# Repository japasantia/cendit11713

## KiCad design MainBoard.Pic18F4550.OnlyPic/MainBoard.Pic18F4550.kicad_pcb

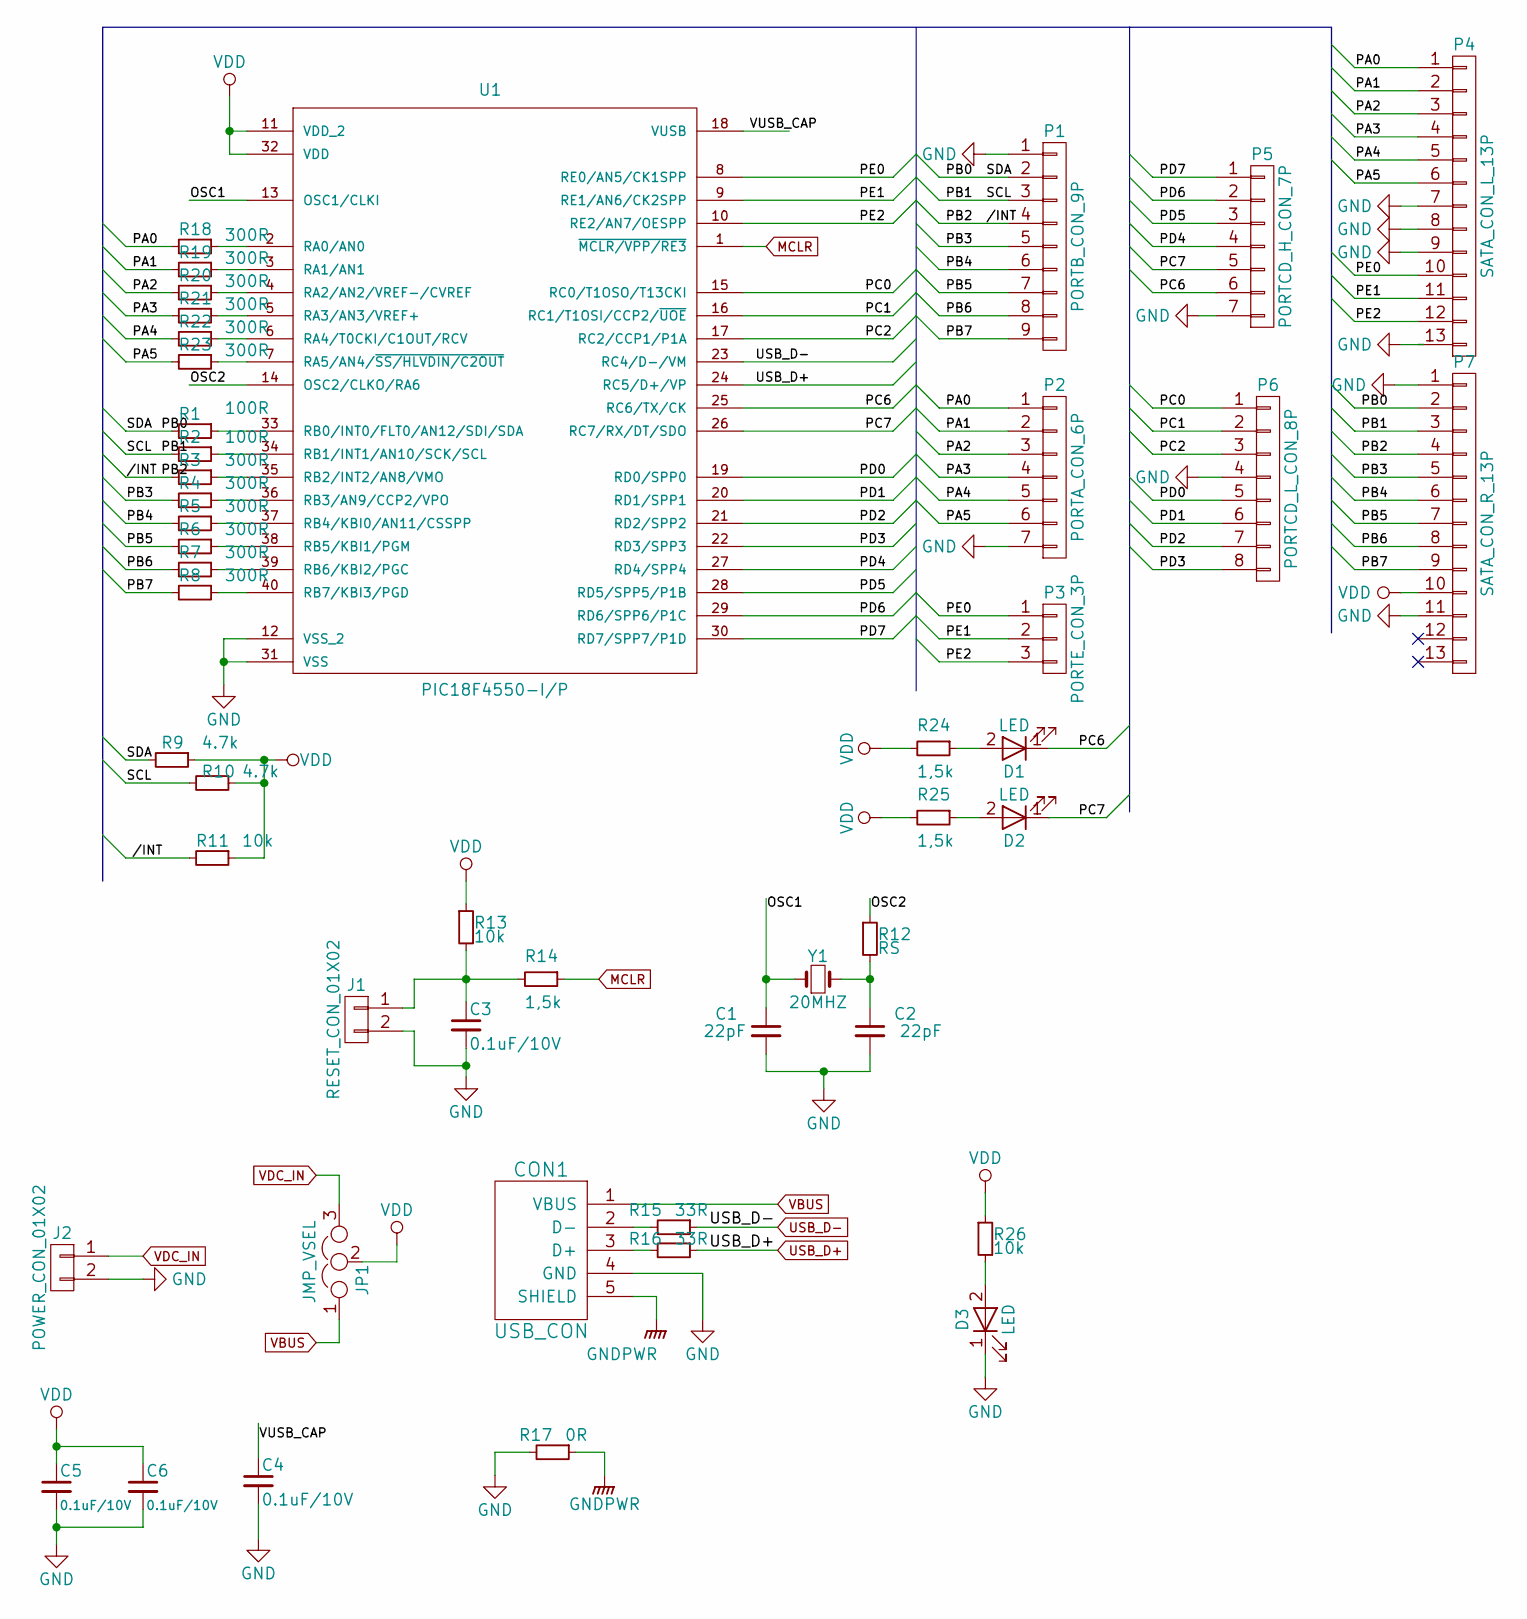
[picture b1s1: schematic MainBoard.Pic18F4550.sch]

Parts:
C1, C2: 22pF; C_0805_HandSoldering
C3, C4: 0.1uF/10V; C_0805_HandSoldering
C5, C6: 0.1uF/10V; C_1206_HandSoldering
CON1: USB_CON; USB_SMT_B
D1, D2, D3: LED; LED_0805
J1: RESET_CON_01X02; Pin_Header_Straight_1x02_Pitch2.54mm
J2: POWER_CON_01X02; Pin_Header_Straight_1x02_Pitch2.54mm
JP1: JMP_VSEL; Pin_Header_Straight_1x03
P1: PORTB_CON_9P; Pin_Header_Straight_1x09
P2: PORTA_CON_6P; Pin_Header_Straight_1x07
P3: PORTE_CON_3P; Pin_Header_Straight_1x03
P4: SATA_CON_L_13P; SLIMLINE_SATA_PLUG_7P_6P
P5: PORTCD_H_CON_7P; Pin_Header_Straight_1x07
P6: PORTCD_L_CON_8P; Pin_Header_Straight_1x08
P7: SATA_CON_R_13P; SATA_RECEPTACLE_VERTICAL_SMT_6P_7P
R1, R2: 100R; R_0805_HandSoldering
R3, R4, R5, R6, R7, R8, R18, R19, R20, R21, R22, R23: 300R; R_0805_HandSoldering
R9, R10: 4.7k; R_0805_HandSoldering
R11, R13, R26: 10k; R_0805_HandSoldering
R12: RS; R_0805_HandSoldering
R14, R24, R25: 1,5k; R_0805_HandSoldering
R15, R16: 33R; R_0805_HandSoldering
R17: 0R; R_0805_HandSoldering
U1: PIC18F4550-I/P; PIC18F4550-PDIP
Y1: 20MHZ; Crystal_SMD_HC49-SD

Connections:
//INT: P1.4, P7.4, R3.2, R11.2
/OSC1: C1.1, U1.13 (OSC1/CLKI), Y1.1
/OSC2: R12.1, U1.14 (OSC2/CLKO/RA6)
/PA0: P2.1, P4.1, R18.2
/PA1: P2.2, P4.2, R19.2
/PA2: P2.3, P4.3, R20.2
/PA3: P2.4, P4.4, R21.2
/PA4: P2.5, P4.5, R22.2
/PA5: P2.6, P4.6, R23.2
/PB0: P1.2, P7.2, R1.2, R9.2
/PB1: P1.3, P7.3, R2.2, R10.2
/PB3: P1.5, P7.5, R4.2
/PB4: P1.6, P7.6, R5.2
/PB5: P1.7, P7.7, R6.2
/PB6: P1.8, P7.8, R7.2
/PB7: P1.9, P7.9, R8.2
/PC0: P6.1, U1.15 (RC0/T1OSO/T13CKI)
/PC1: P6.2, U1.16 (RC1/T1OSI/CCP2/~UOE)
/PC2: P6.3, U1.17 (RC2/CCP1/P1A)
/PC6: D1.1 (K), P5.6, U1.25 (RC6/TX/CK)
/PC7: D2.1 (K), P5.5, U1.26 (RC7/RX/DT/SDO)
/PD0: P6.5, U1.19 (RD0/SPP0)
/PD1: P6.6, U1.20 (RD1/SPP1)
/PD2: P6.7, U1.21 (RD2/SPP2)
/PD3: P6.8, U1.22 (RD3/SPP3)
/PD4: P5.4, U1.27 (RD4/SPP4)
/PD5: P5.3, U1.28 (RD5/SPP5/P1B)
/PD6: P5.2, U1.29 (RD6/SPP6/P1C)
/PD7: P5.1, U1.30 (RD7/SPP7/P1D)
/PE0: P3.1, P4.10, U1.8 (RE0/AN5/CK1SPP)
/PE1: P3.2, P4.11, U1.9 (RE1/AN6/CK2SPP)
/PE2: P3.3, P4.12, U1.10 (RE2/AN7/OESPP)
/VUSB_CAP: C4.1, U1.18 (VUSB)
GND: C1.2, C2.2, C3.2, C4.2, C5.2, C6.2, CON1.4 (GND), D3.1 (K), J1.2, J2.2, P1.1, P2.7, P4.7, P4.8, P4.9, P5.7, P6.4, P7.1, P7.11, R17.2, U1.12 (VSS_2), U1.31 (VSS)
GNDPWR: CON1.5 (SHIELD), R17.1
MCLR: R14.1, U1.1 (~MCLR/VPP/RE3)
unnamed: C2.1, R12.2, Y1.2
unnamed: C3.1, J1.1, R13.2, R14.2
unnamed: CON1.2 (D-), R15.2
unnamed: CON1.3 (D+), R16.2
unnamed: D1.2 (A), R24.1
unnamed: D2.2 (A), R25.1
unnamed: D3.2 (A), R26.2
unnamed: R1.1, U1.33 (RB0/INT0/FLT0/AN12/SDI/SDA)
unnamed: R2.1, U1.34 (RB1/INT1/AN10/SCK/SCL)
unnamed: R3.1, U1.35 (RB2/INT2/AN8/VMO)
unnamed: R4.1, U1.36 (RB3/AN9/CCP2/VPO)
unnamed: R5.1, U1.37 (RB4/KBI0/AN11/CSSPP)
unnamed: R6.1, U1.38 (RB5/KBI1/PGM)
unnamed: R7.1, U1.39 (RB6/KBI2/PGC)
unnamed: R8.1, U1.40 (RB7/KBI3/PGD)
unnamed: R18.1, U1.2 (RA0/AN0)
unnamed: R19.1, U1.3 (RA1/AN1)
unnamed: R20.1, U1.4 (RA2/AN2/VREF-/CVREF)
unnamed: R21.1, U1.5 (RA3/AN3/VREF+)
unnamed: R22.1, U1.6 (RA4/T0CKI/C1OUT/RCV)
unnamed: R23.1, U1.7 (RA5/AN4/~SS/HLVDIN/C2OUT)
USB_D+: R16.1, U1.24 (RC5/D+/VP)
USB_D-: R15.1, U1.23 (RC4/D-/VM)
VBUS: CON1.1 (VBUS), JP1.1
VDC_IN: J2.1, JP1.3
VDD: C5.1, C6.1, JP1.2, P7.10, R9.1, R10.1, R11.1, R13.1, R24.2, R25.2, R26.1, U1.11 (VDD_2), U1.32 (VDD)

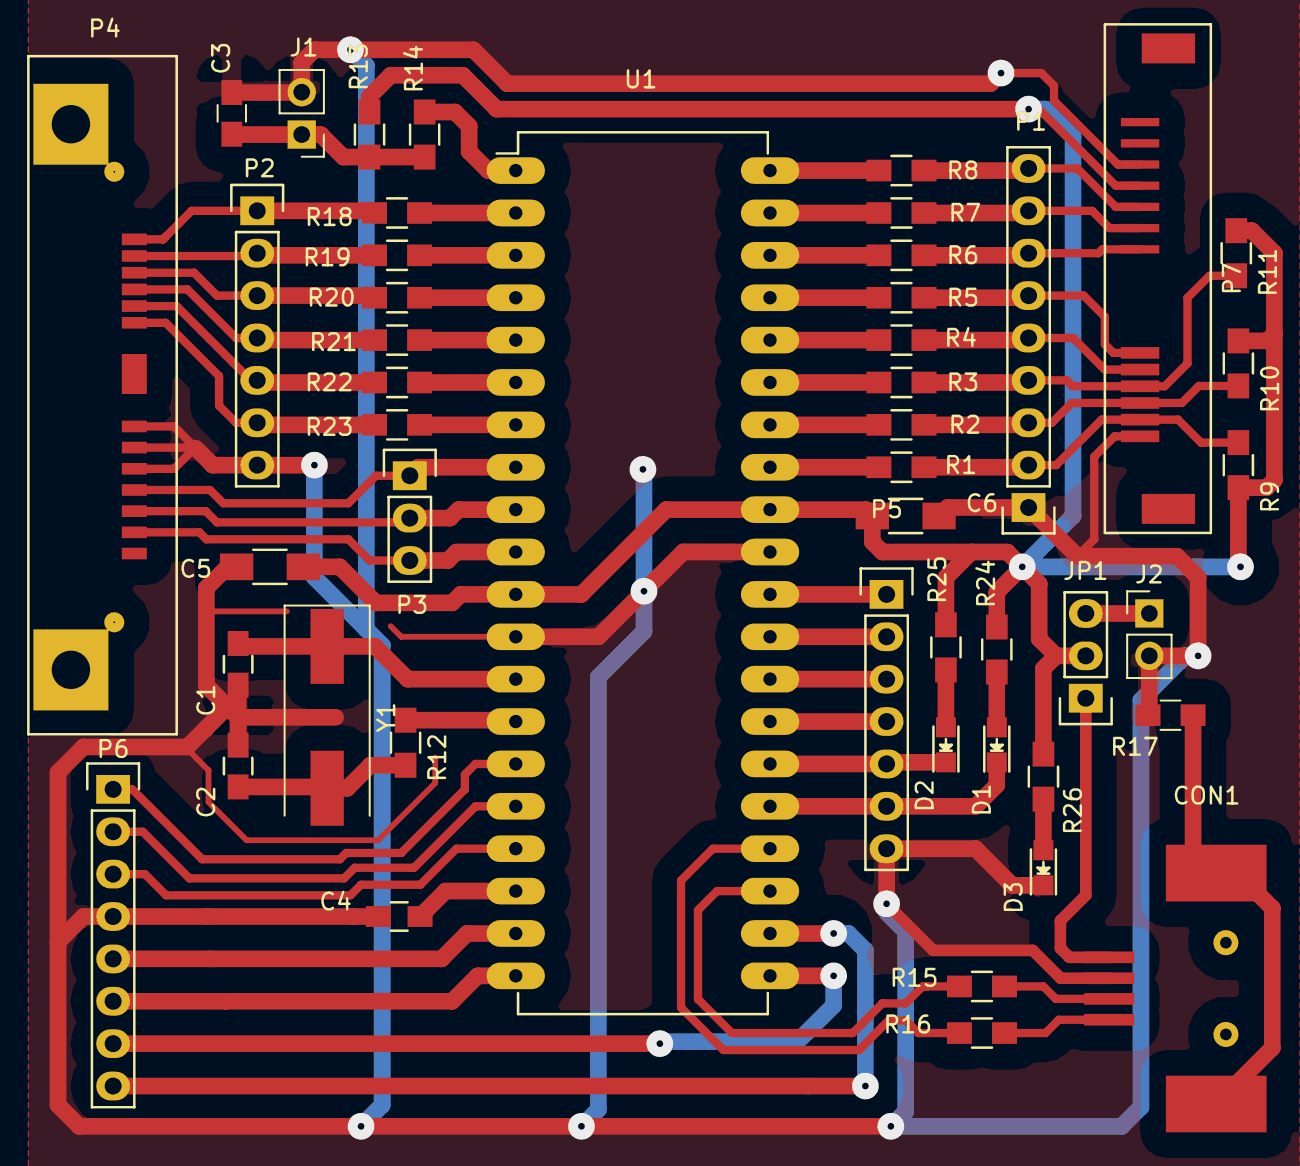
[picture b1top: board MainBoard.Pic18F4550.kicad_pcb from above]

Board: 2 copper layers, 48 parts (0 on the bottom side), 62 nets.

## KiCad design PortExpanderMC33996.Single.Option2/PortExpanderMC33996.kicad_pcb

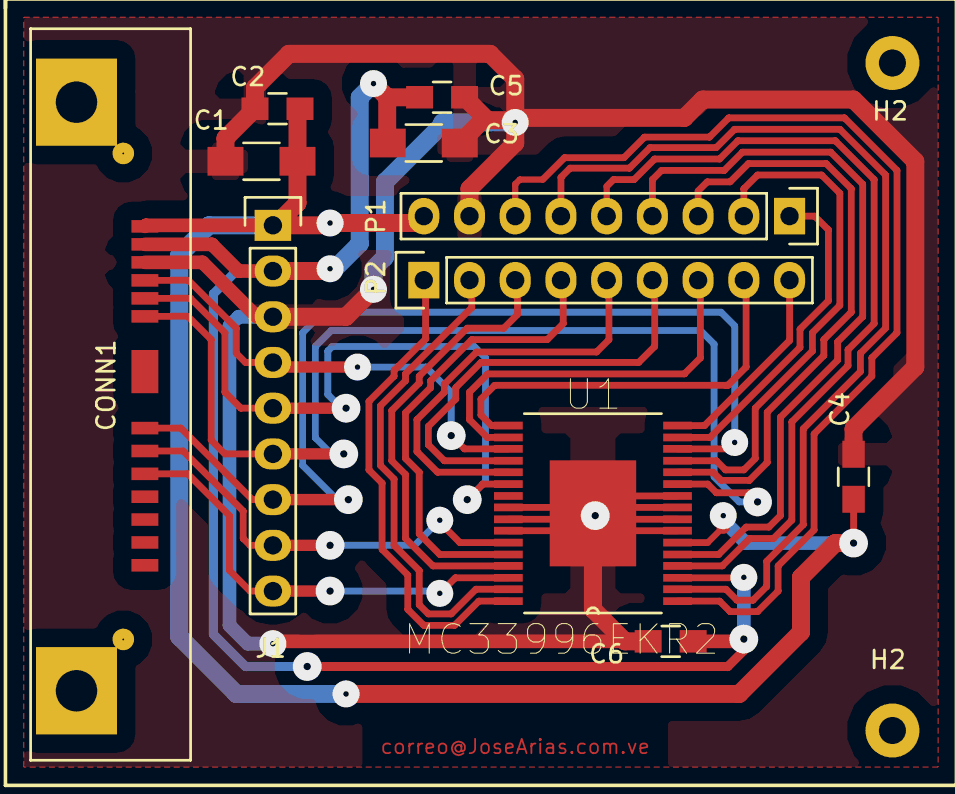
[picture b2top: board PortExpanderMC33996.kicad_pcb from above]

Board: 2 copper layers, 13 parts (0 on the bottom side), 25 nets.

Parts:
C1, C3: 10uF; C_1206_HandSoldering
C2, C4, C5, C6: 0.1uF; C_0805_HandSoldering
CONN1: VIKING_SPI_BUS; SLIMLINE_SATA_PLUG_7P_6P
H2, H2#2: HOLE_3MM
J1: DEBUG_CONN; Pin_Header_Straight_1x09
P1, P2: VIKING_HEADER_9P; Pin_Header_Straight_1x09
U1: MC33996EKR2

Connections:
//CS: CONN1.7, J1.7, U1.14
//RESET: CONN1.8, J1.8, U1.27
/MISO: CONN1.5, J1.5, U1.22
/MOSI: CONN1.4, J1.4, U1.19
/P0: P1.7, U1.1
/P1: P1.6, U1.2
/P2: P1.5, U1.4
/P3: P1.4, U1.5
/P4: P1.3, U1.12
/P5: P1.2, U1.13
/P6: P1.1, U1.15
/P7: P2.9, U1.16
/P8: P2.8, U1.17
/P9: P2.7, U1.18
/P10: P2.6, U1.20
/P11: P2.5, U1.21
/P12: P2.4, U1.28
/P13: P2.3, U1.29
/P14: P2.2, U1.31
/P15: P2.1, U1.32
/PWM: CONN1.9, J1.9, U1.30
/SCLK: CONN1.6, J1.6, U1.11
GNDPWR: C1.2, C2.2, C3.2, C4.2, C5.2, C6.2, CONN1.3, J1.3, P1.8, U1.7, U1.8, U1.9, U1.10, U1.24, U1.25, U1.26, U1.33
VCC: C3.1, C5.1, C6.1, CONN1.2, J1.2, U1.3
VPP: C1.1, C2.1, C4.1, CONN1.1, J1.1, P1.9, U1.6
